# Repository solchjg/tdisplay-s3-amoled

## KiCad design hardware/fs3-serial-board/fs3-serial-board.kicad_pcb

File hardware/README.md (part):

# Hardware: producing the FeatherS3D survey boards

This folder holds three boards for the FeatherS3D site survey and the §40 build,
plus the generator that makes them. This page lists the steps from the design files
to a working set of boards. The design itself, and the reasons behind it, are in
[fs3-survey-carrier.md](../docs/Method/project/fs3-survey-carrier.md). Wiring sheets
[17](../docs/Method/project/wiring/wiring-17-fs3-carrier.png),
[19](../docs/Method/project/wiring/wiring-19-fs3-analog.png) and
[20](../docs/Method/project/wiring/wiring-20-fs3-serial.png) (where each part sits on the
carrier, the analog board and the serial board) and
[18](../docs/Method/project/wiring/wiring-18-fs3-boards.png) (the leads between the boards)
show how the boards fit together.

| Folder | Board | Size | Plugs into |
|---|---|---|---|
| [`fs3-survey-carrier/`](fs3-survey-carrier/) | The carrier: FeatherS3D on sockets, Notecarrier-X on posts, every connector | 110 × 90 mm | — |
| [`fs3-analog-board/`](fs3-analog-board/) | Isolated 4-20 mA loop and 0 – 5 V probe input (24 V field supply, ADS1115) | 74 × 54 mm | Carrier J12 |
| [`fs3-serial-board/`](fs3-serial-board/) | Isolated logic-level serial port for the MB7569 ultrasonic sensor | 63 × 54 mm | Carrier J13 |
| [`pcbgen/`](pcbgen/) | The shared scripts that make all three from each board's `netlist.py` | — | — |

Each board's `fab/` folder holds what a board house and an assembler need:

| File | Use |
|---|---|
| `<board>-gerbers.zip` | Gerbers and drill files, for the board house |
| `bom.csv` | The parts list: quantity, value, designators, footprint, part number |
| `positions.csv` | Part placement for an assembly service (origin at the bottom-left corner) |
| `cpl-jlc.csv`, `bom-jlc.csv` | The surface-mount parts' placement (CPL) and parts list in JLCPCB's columns |
| `cpl-jlc-all.csv`, `bom-jlc-all.csv` | The same for every fitted part, through-hole connectors, sockets and the key included |
| `centroid-pcbway.csv`, `bom-pcbway.csv` | Every fitted part's placement (centroid) and parts list in PCBWay's columns, each line marked SMD or THT |
| `assembly.pdf` | The top side with each part's designator, for hand assembly and for the fit checks below |
| `schematic.pdf` | The schematic |
| `top.png`, `bottom.png` | Pictures of the finished board |

## 1. Close the open checks

None of the boards has been built yet. Settle these before ordering. Each one is
explained in "Before ordering" in
[fs3-survey-carrier.md](../docs/Method/project/fs3-survey-carrier.md#before-ordering).

- [ ] **Notecarrier-X holes.** Check that a Notecarrier-X v1.3 has the v1.2 drawing's
      holes (58.49 × 30.48 mm) and that M2.5 posts fit them.
- [ ] **Feather footprint.** Print the carrier's `assembly.pdf` at 100 % and lay the
      FeatherS3D on it. RST (long header pin 1) must sit at the USB-C end, and BAT must be
      level with the long header's fifth pin.
- [ ] **Display cables.** Use a same-direction 8-way PH 2.0 lead for the e-paper (pin 1 to
      pin 1) and a standard straight 16-way IDC ribbon for the 3.12" OLED. Check that the OLED
      module's pin 3 is unconnected.
- [ ] **Qwiic pinout.** Pin 1 is GND and pin 4 is SCL.
- [ ] **Isolated DC-DCs.** Check the test duration of XP Power's IH "-H" 3 kVDC rating
      against C-40.6's 1 minute, and the IH0512S-H's pins against XP's drawing.
- [ ] **FSD §40.2.** It still names the Pololu #2808 as the display supply. The carrier
      uses an on-board TPS22917 instead. If you adopt the carrier, change that row in the FSD.

## 2. Order the boards

Upload each `fab/<board>-gerbers.zip` to a board house (JLCPCB, PCBWay, OSH Park and
similar). The settings are the same for all three:

- 2 layers, 1.6 mm FR-4, 1 oz copper
- HASL (lead-free) or ENIG finish, any solder mask colour
- Default rules: 0.2 mm (8 mil) track and space, 0.3 mm smallest drill
- No impedance control, no castellations, no V-scoring

The minimum order (usually 5) of each board is enough for spares.

To have the board house fit the surface-mount parts too, upload the BOM and placement
files with the Gerbers and fit the through-hole parts yourself afterwards:

- **JLCPCB:** `bom-jlc.csv` and `cpl-jlc.csv` hold only the surface-mount parts;
  `bom-jlc-all.csv` and `cpl-jlc-all.csv` add the through-hole parts, for JLCPCB to fit
  those too (at extra cost; check that each through-hole part is one it stocks).
  The `LCSC Part #` column is empty: fill it in, or pick each part in JLCPCB's matcher,
  checking it against the part number in the `Comment` column. In the placement
  preview, check each part's rotation and pin 1, above all the SOT-23, SOIC and TSSOP
  parts, the diodes and the Qwiic and microSD sockets. JLCPCB's library draws some
  footprints turned from KiCad's, and the preview lets you rotate a part to fix it.
- **PCBWay:** `bom-pcbway.csv` and `centroid-pcbway.csv`. They list every fitted part;
  the `Type` column says which are SMD and which THT, so you can delete the THT lines or
  note "do not place" against them to fit those parts yourself. Check rotations in the
  engineering query PCBWay sends before assembly, as for JLCPCB.
- **Other assemblers:** `bom.csv` and `positions.csv` (KiCad's format, all parts).

## 3. Order the parts

Each board's `bom.csv` lists its parts with a part number, or a generic description
for passives. The parts that need care when buying:

| Part | Board | Note |
|---|---|---|
| TPS22917DBVR | Carrier | Display supply switch; no substitute with the same pins |
| Molex 104031-0811 | Carrier | The microSD socket; its footprint is specific to it |
| Littelfuse 0466003.NR | Carrier | F1, the shared battery's 3 A fuse (1206) |
| XP Power IH0512S-H, IH0505S-H | Analog, serial | The isolated DC-DCs; the "-H" suffix is the 3 kVDC version |
| TI ISO1642DWR | Analog, serial | I2C isolator, wide SOIC-16 |
| TI ADS1115IDGSR | Analog | MSOP-10 with 0.5 mm pitch |
| Microchip DN2540N3-G | Analog | Current limiters, TO-92 |
| Vishay TNPW1206100RBEEA | Analog | R2, the 100 Ω 0.1 % loop shunt |
| 15 kΩ and 10 kΩ, 0.1 % | Analog | R14 and R15, the probe divider |
| Bourns 3296W-1-201LF | Analog | RV1 and RV2, 200 Ω trimmers |
| Phoenix MKDS 1,5 (5.08 mm) | Analog, serial | Field terminals: 2-way and 3-way (analog), 4-way (serial) |

Besides the boards' own parts, the build needs:

- **Feather sockets:** a 1 × 16 and a 1 × 12 2.54 mm female socket strip (in the BOM as
  J1 and J2).
- **Posts:** four M2.5 standoffs, at least 10 mm, for the Notecarrier-X; four M3 standoffs
  for the carrier's corners; four M3 standoffs for each add-on board.
- **Leads**, all straight (pin 1 to pin 1):
  - JST XH 6-way (carrier J12 to the analog board) and XH 4-way (J13 to the serial board)
  - JST XH 3-way for the key (J3)
  - JST PH 2-way leads from J23 to the Feather's battery socket and from J25 to the
    Notecarrier's, or one XH 2-way lead from J27 to the Notecarrier header for the
    shared battery (at most 150 mm, 22 AWG or heavier)
  - JST PH 2.0 8-way for the e-paper, or a 16-way IDC ribbon for the 3.12" OLED
  - Qwiic (JST SH 4-way) leads for the Feather's I2C2 socket, the RTC, the Notecarrier,
    the BME280 and the 1.3" OLED
- **Jumpers:** two 2.54 mm jumpers for J26, or a panel DPST switch and its lead.
- **Enclosure side:** a waterproof panel-mount USB-C socket; surge protectors and an earth
  rod for each field cable (C-40.7), which stay at the enclosure wall, not on the boards;
  cable glands.

## 4. Assemble

- **Carrier.** Solder the surface-mount parts first, then the through-hole connectors
  and the Feather socket strips. Leave JP1 open, so the Notecarrier's 3.3 V stays
  unconnected. Do not fit a cell to J24 or the Notecarrier's own socket if you will use
  the shared battery on J27.
- **Analog and serial boards.** Solder the surface-mount parts first. The ADS1115 has
  0.5 mm pitch and needs flux and a fine tip, or a hot-air station. Fit the DC-DC, the
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
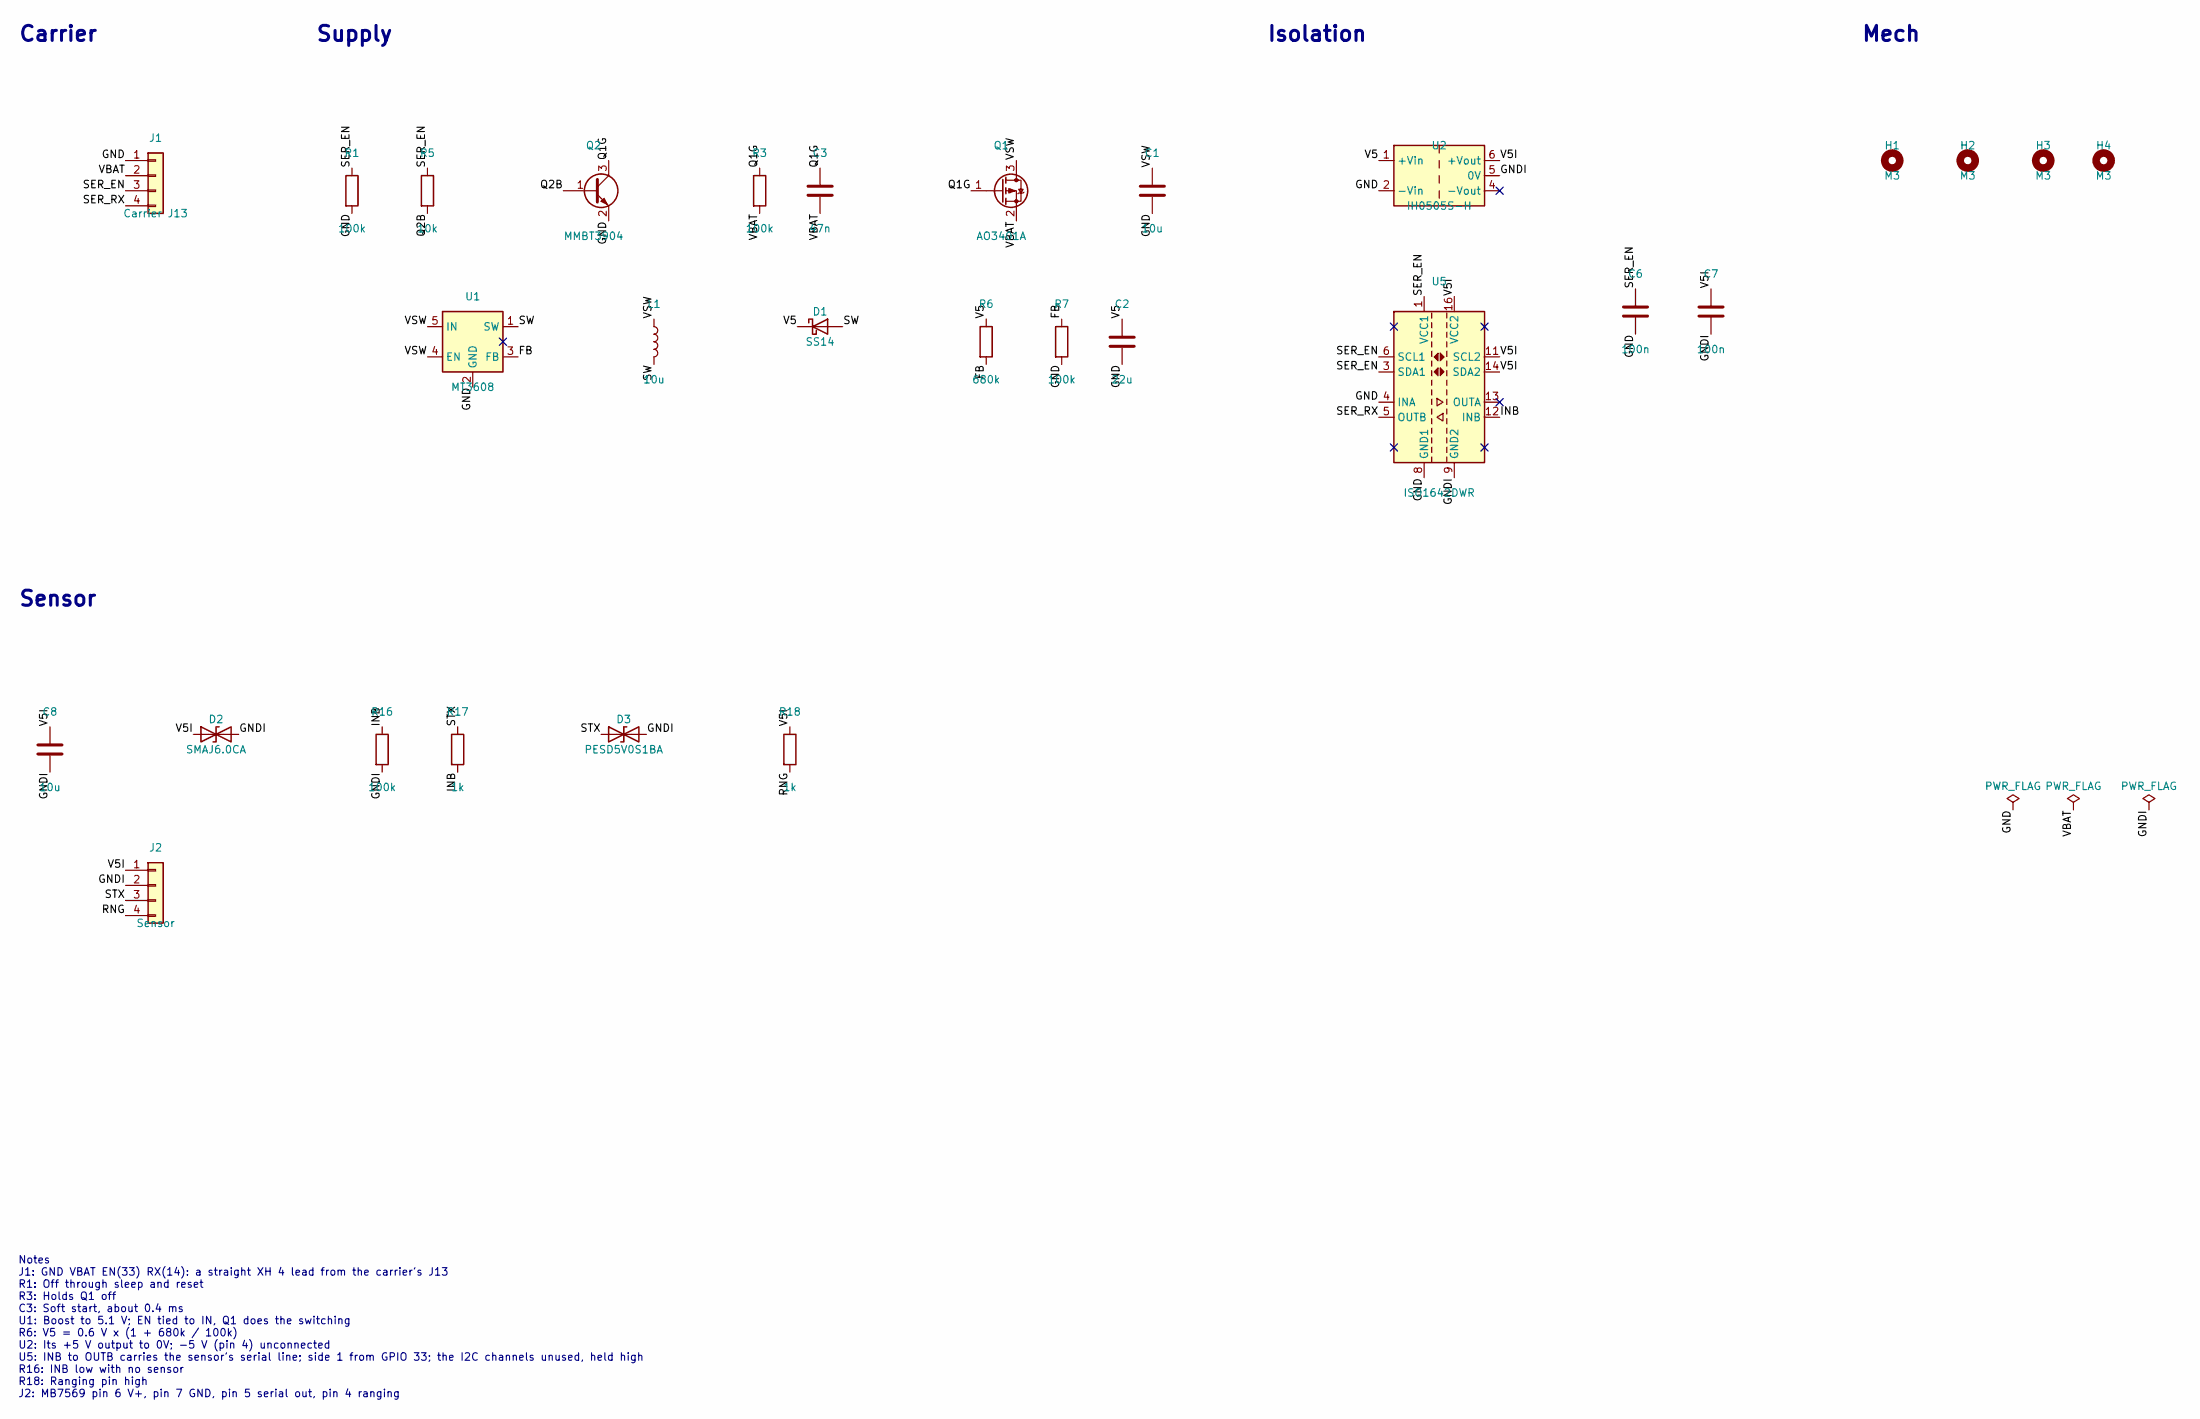
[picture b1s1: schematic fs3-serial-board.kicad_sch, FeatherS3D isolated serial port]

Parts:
C1, C8: 10u; C_0805_2012Metric
C2: 22u; C_1206_3216Metric; MPN 22 uF 1206 X5R 10 V
C3: 47n; C_0805_2012Metric
C6, C7: 100n; C_0805_2012Metric
D1: SS14; D_SMA; MPN SS14 (1 A, 40 V Schottky)
D2: SMAJ6.0CA; D_SMA; MPN SMAJ6.0CA
D3: PESD5V0S1BA; D_SOD-323; MPN Nexperia PESD5V0S1BA
H1, H2, H3, H4: M3; MountingHole_3.2mm_M3
J1: Carrier J13; JST_XH_B4B-XH-A_1x04_P2.50mm_Vertical; MPN JST B4B-XH-A
J2: Sensor; TerminalBlock_Phoenix_MKDS-1,5-4-5.08_1x04_P5.08mm_Horizont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; MPN Phoenix 1715747 (MKDS 1,5/4-5,08)
L1: 10u; L_Bourns_SRN6045TA; MPN Bourns SRN6045TA-100M (10 uH, 2.4 A)
Q1: AO3401A; SOT-23; MPN Alpha & Omega AO3401A (or DMG2305UX)
Q2: MMBT3904; SOT-23; MPN onsemi MMBT3904LT1G
R1, R3, R7, R16: 100k; R_0805_2012Metric
R5: 10k; R_0805_2012Metric
R6: 680k; R_0805_2012Metric
R17, R18: 1k; R_0805_2012Metric
U1: MT3608; SOT-23-6; MPN Aerosemi MT3608
U2: IH0505S-H; Converter_DCDC_XP_POWER-IHxxxxSH_THT; MPN XP Power IH0505S-H (2 W, 3 kVDC)
U5: ISO1642DWR; SOIC-16W_7.5x10.3mm_P1.27mm; MPN TI ISO1642DWR (5 kVrms)

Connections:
FB: R6.2, R7.1, U1.3 (FB)
GND: C1.2, C2.2, C6.2, J1.1, Q2.2 (E), R1.2, R7.2, U1.2 (GND), U2.2 (-Vin), U5.4 (INA), U5.8 (GND1)
GNDI: C7.2, C8.2, D2.2 (A2), D3.2 (A2), J2.2, R16.2, U2.5 (0V), U5.9 (GND2)
INB: R16.1, R17.2, U5.12 (INB)
Q1G: C3.1, Q1.1 (G), Q2.3 (C), R3.1
Q2B: Q2.1 (B), R5.2
RNG: J2.4, R18.2
SER_EN: C6.1, J1.3, R1.1, R5.1, U5.1 (VCC1), U5.3 (SDA1), U5.6 (SCL1)
SER_RX: J1.4, U5.5 (OUTB)
STX: D3.1 (A1), J2.3, R17.1
SW: D1.2 (A), L1.2, U1.1 (SW)
V5: C2.1, D1.1 (K), R6.1, U2.1 (+Vin)
V5I: C7.1, C8.1, D2.1 (A1), J2.1, R18.1, U2.6 (+Vout), U5.11 (SCL2), U5.14 (SDA2), U5.16 (VCC2)
VBAT: C3.2, J1.2, Q1.2 (S), R3.2
VSW: C1.1, L1.1, Q1.3 (D), U1.4 (EN), U1.5 (IN)

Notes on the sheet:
Notes J1: GND VBAT EN(33) RX(14): a straight XH 4 lead from the carrier's J13 R1: Off through sleep and reset R3: Holds Q1 off C3: Soft start, about 0.4 ms U1: Boost to 5.1 V; EN tied to IN, Q1 does the switching R6: V5 = 0.6 V x (1 + 680k / 100k) U2: Its +5 V output to 0V; -5 V (pin 4) unconnected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
Carrier
Supply
Isolation
Sensor
Mech

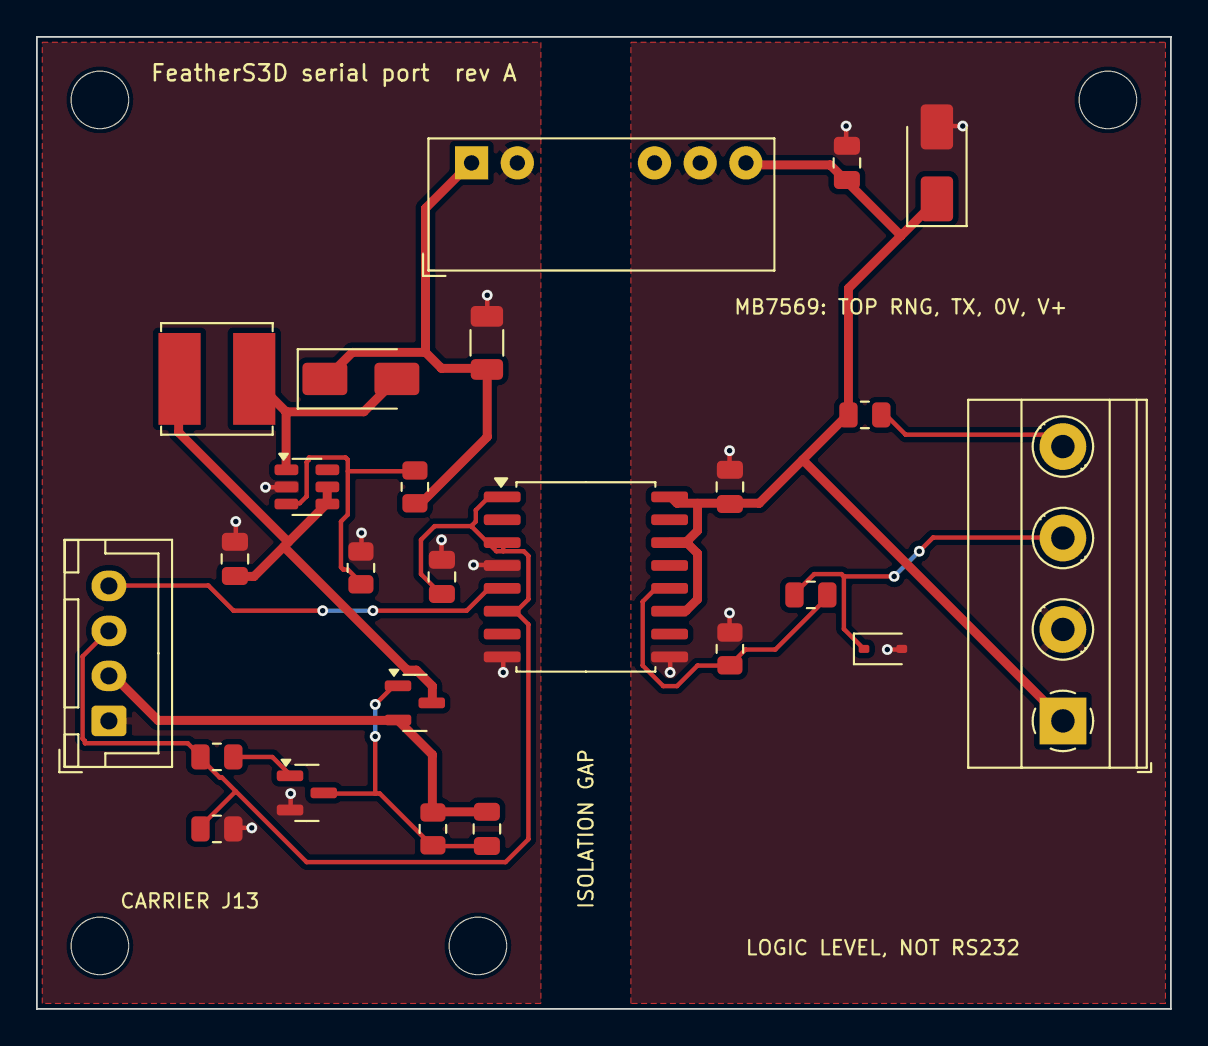
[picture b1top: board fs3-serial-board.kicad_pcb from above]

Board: 2 copper layers, 63.0 x 54.0 mm, 29 parts (0 on the bottom side), 15 nets.

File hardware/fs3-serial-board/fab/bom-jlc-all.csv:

Comment,Designator,Footprint,LCSC Part #
10u 0805 X5R 10 V,"C1,C8",C_0805_2012Metric,
22 uF 1206 X5R 10 V,C2,C_1206_3216Metric,
47n 0805 X7R 16 V,C3,C_0805_2012Metric,
100n 0805 X7R 50 V,"C6,C7",C_0805_2012Metric,
"SS14 (1 A, 40 V Schottky)",D1,D_SMA,
SMAJ6.0CA,D2,D_SMA,
Nexperia PESD5V0S1BA,D3,D_SOD-323,
JST B4B-XH-A,J1,JST_XH_B4B-XH-A_1x04_P2.50mm_Vertical,
"Phoenix 1715747 (MKDS 1,5/4-5,08)",J2,"TerminalBlock_Phoenix_MKDS-1,5-4-5.08_1x04_P5.08mm_Horizontal",
"Bourns SRN6045TA-100M (10 uH, 2.4 A)",L1,L_Bourns_SRN6045TA,
Alpha & Omega AO3401A (or DMG2305UX),Q1,SOT-23,
onsemi MMBT3904LT1G,Q2,SOT-23,
100k 0805 1 %,"R1,R3,R7,R16",R_0805_2012Metric,
10k 0805 1 %,R5,R_0805_2012Metric,
680k 0805 1 %,R6,R_0805_2012Metric,
1k 0805 1 %,"R17,R18",R_0805_2012Metric,
Aerosemi MT3608,U1,SOT-23-6,
"XP Power IH0505S-H (2 W, 3 kVDC)",U2,Converter_DCDC_XP_POWER-IHxxxxSH_THT,
TI ISO1642DWR (5 kVrms),U5,SOIC-16W_7.5x10.3mm_P1.27mm,

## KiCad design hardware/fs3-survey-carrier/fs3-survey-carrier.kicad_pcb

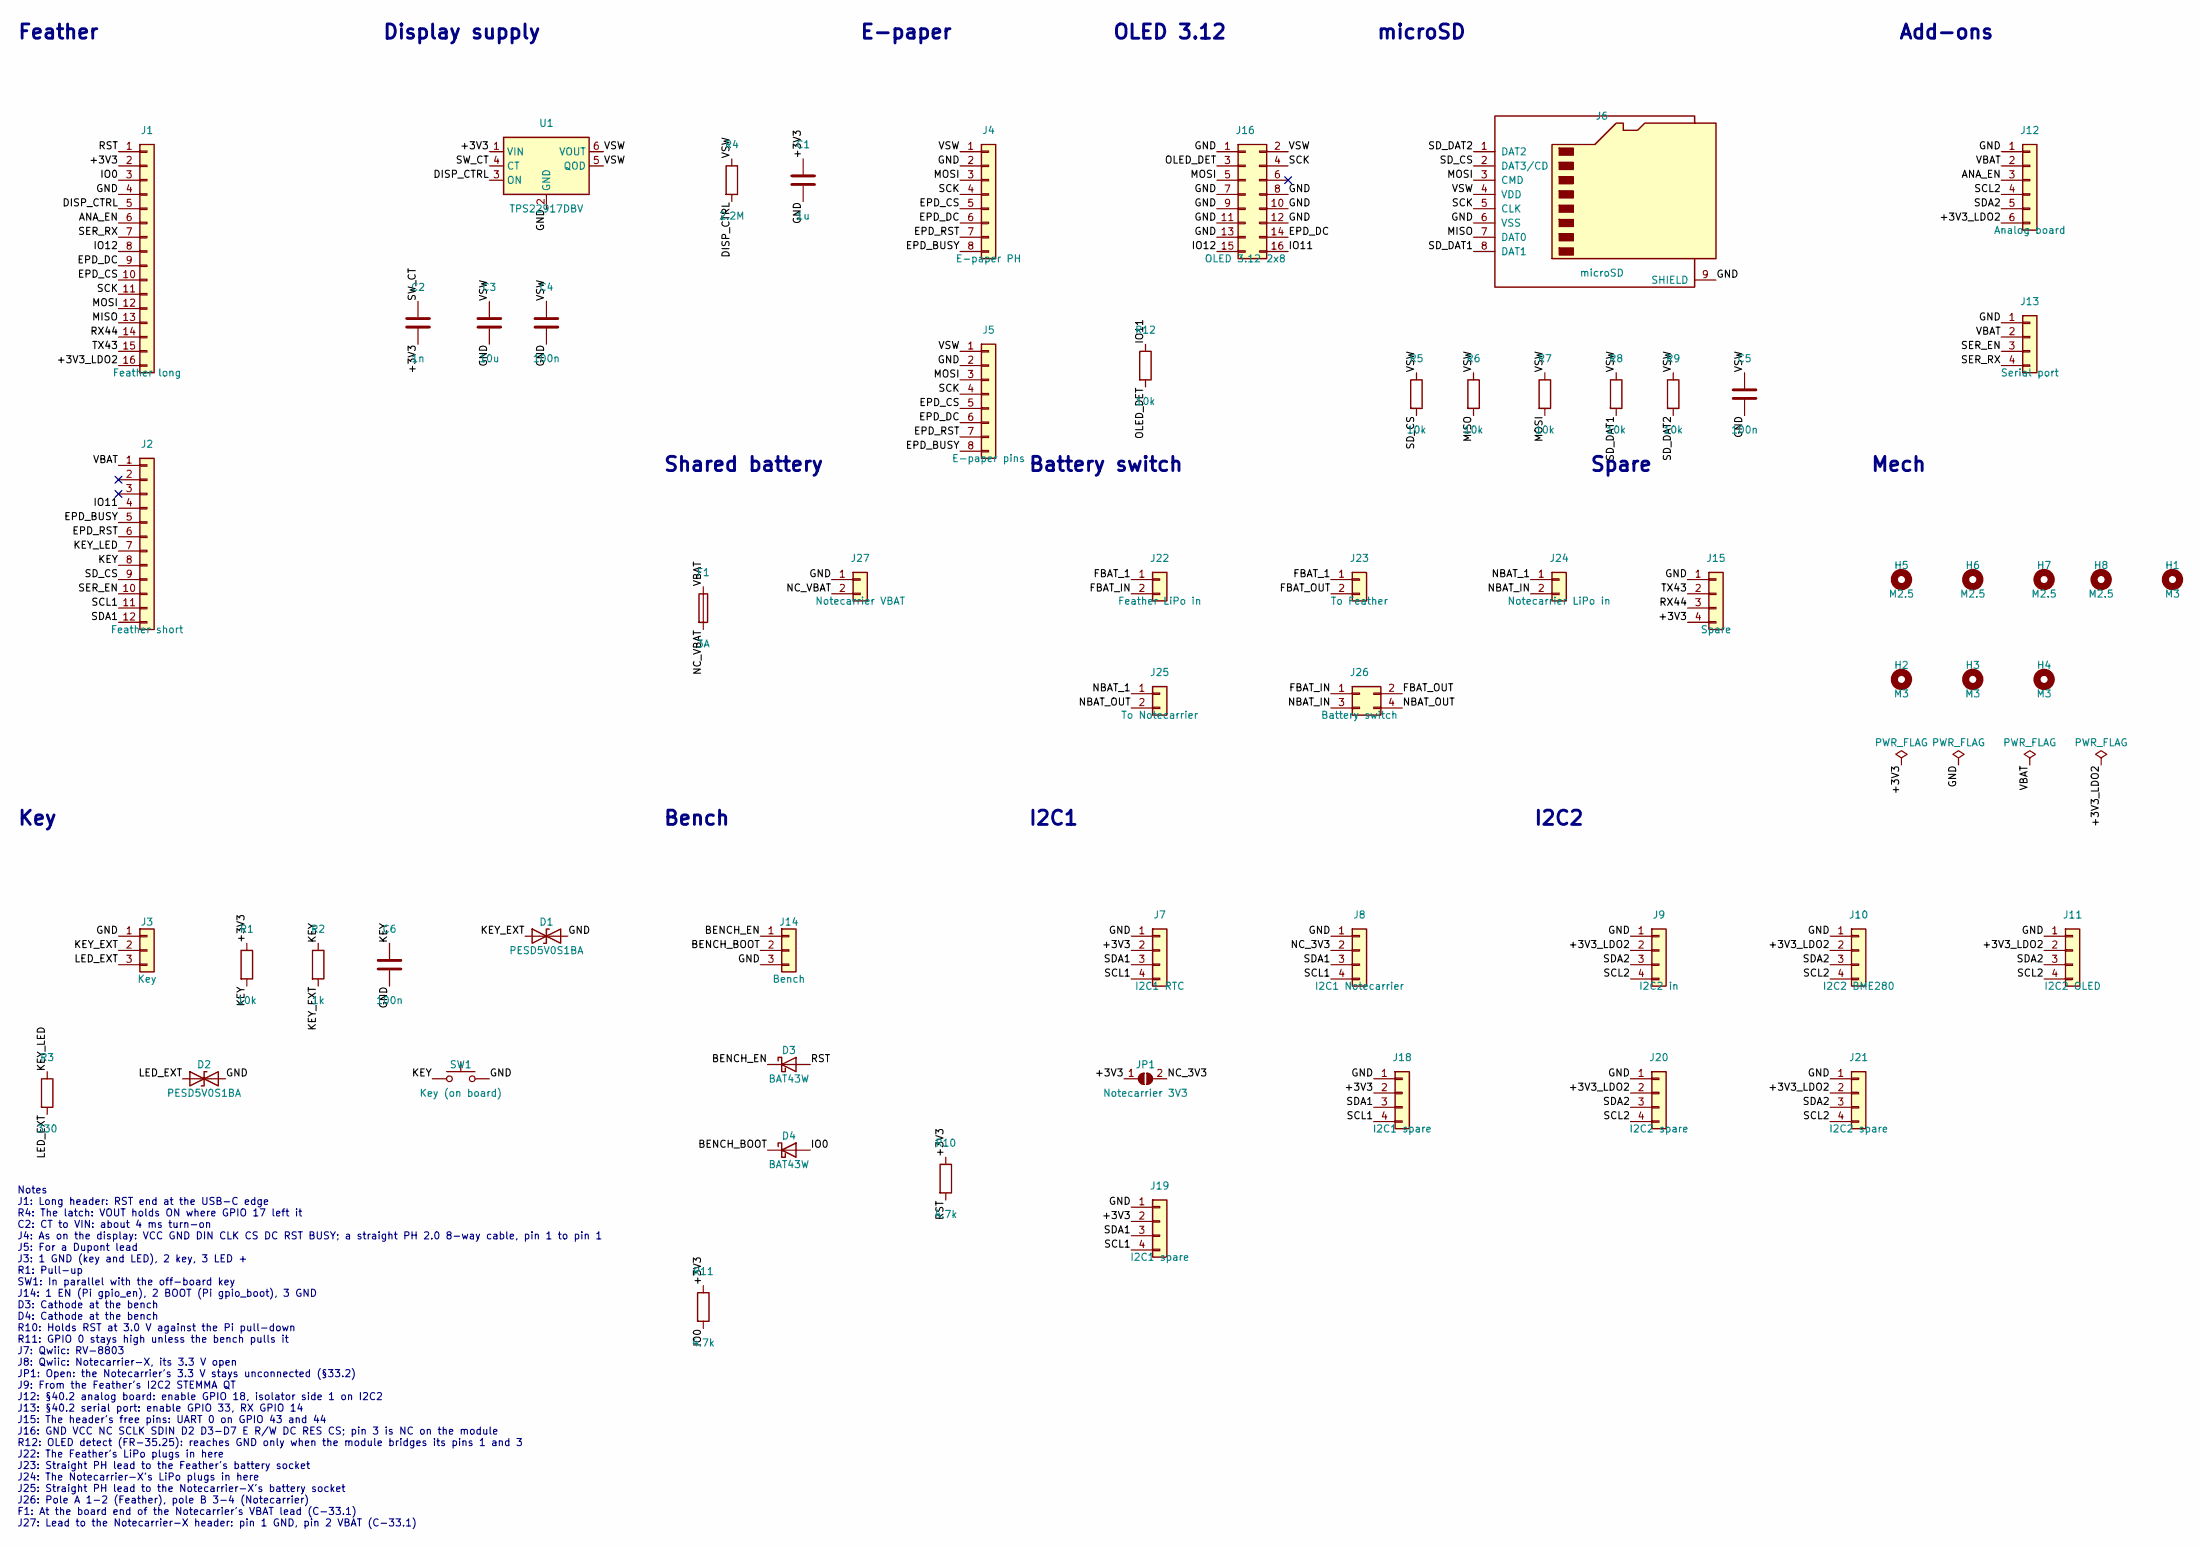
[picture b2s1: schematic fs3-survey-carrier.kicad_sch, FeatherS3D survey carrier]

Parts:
C1: 1u; C_0805_2012Metric
C2: 1n; C_0805_2012Metric
C3: 10u; C_0805_2012Metric
C4, C5, C6: 100n; C_0805_2012Metric
D1, D2: PESD5V0S1BA; D_SOD-323; MPN Nexperia PESD5V0S1BA
D3, D4: BAT43W; D_SOD-123; MPN BAT43W
F1: 3A; Fuse_1206_3216Metric; MPN Littelfuse 0466003.NR (3 A fast, 1206)
H1, H2, H3, H4: M3; MountingHole_3.2mm_M3
H5, H6, H7, H8: M2.5; MountingHole_2.7mm_M2.5
J1: Feather long; PinSocket_1x16_P2.54mm_Vertical; MPN Samtec SSW-116-01-T-S or any 1x16 2.54 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
J2: Feather short; PinSocket_1x12_P2.54mm_Vertical; MPN 1x12 2.54 mm socket
J3: Key; JST_XH_B3B-XH-A_1x03_P2.50mm_Vertical; MPN JST B3B-XH-A
J4: E-paper PH; JST_PH_B8B-PH-K_1x08_P2.00mm_Vertical; MPN JST B8B-PH-K-S
J5: E-paper pins; PinHeader_1x08_P2.54mm_Vertical; MPN 1x8 2.54 mm header
J6: microSD; microSD_HC_Molex_104031-0811; MPN Molex 104031-0811
J7: I2C1 RTC; JST_SH_SM04B-SRSS-TB_1x04-1MP_P1.00mm_Horizontal; MPN JST SM04B-SRSS-TB
J8: I2C1 Notecarrier; JST_SH_SM04B-SRSS-TB_1x04-1MP_P1.00mm_Horizontal; MPN JST SM04B-SRSS-TB
J9: I2C2 in; JST_SH_SM04B-SRSS-TB_1x04-1MP_P1.00mm_Horizontal; MPN JST SM04B-SRSS-TB
J10: I2C2 BME280; JST_SH_SM04B-SRSS-TB_1x04-1MP_P1.00mm_Horizontal; MPN JST SM04B-SRSS-TB
J11: I2C2 OLED; JST_SH_SM04B-SRSS-TB_1x04-1MP_P1.00mm_Horizontal; MPN JST SM04B-SRSS-TB
J12: Analog board; JST_XH_B6B-XH-A_1x06_P2.50mm_Vertical; MPN JST B6B-XH-A
J13: Serial port; JST_XH_B4B-XH-A_1x04_P2.50mm_Vertical; MPN JST B4B-XH-A
J14: Bench; PinHeader_1x03_P2.54mm_Vertical; MPN 1x3 2.54 mm header
J15: Spare; PinHeader_1x04_P2.54mm_Vertical; MPN 1x4 2.54 mm header
J16: OLED 3.12 2x8; IDC-Header_2x08_P2.54mm_Vertical; MPN 2x8 2.54 mm shrouded box header (e.g. A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
J18, J19: I2C1 spare; JST_SH_SM04B-SRSS-TB_1x04-1MP_P1.00mm_Horizontal; MPN JST SM04B-SRSS-TB
J20, J21: I2C2 spare; JST_SH_SM04B-SRSS-TB_1x04-1MP_P1.00mm_Horizontal; MPN JST SM04B-SRSS-TB
J22: Feather LiPo in; JST_PH_B2B-PH-K_1x02_P2.00mm_Vertical; MPN JST B2B-PH-K-S
J23: To Feather; JST_PH_B2B-PH-K_1x02_P2.00mm_Vertical; MPN JST B2B-PH-K-S
J24: Notecarrier LiPo in; JST_PH_B2B-PH-K_1x02_P2.00mm_Vertical; MPN JST B2B-PH-K-S
J25: To Notecarrier; JST_PH_B2B-PH-K_1x02_P2.00mm_Vertical; MPN JST B2B-PH-K-S
J26: Battery switch; PinHeader_2x02_P2.54mm_Vertical; MPN 2x2 2.54 mm header + 2 jumpers
J27: Notecarrier VBAT; JST_XH_B2B-XH-A_1x02_P2.50mm_Vertical; MPN JST B2B-XH-A
JP1: Notecarrier 3V3; SolderJumper-2_P1.3mm_Open_RoundedPad1.0x1.5mm
R1, R5, R6, R7, R8, R9, R12: 10k; R_0805_2012Metric
R2: 1k; R_0805_2012Metric
R3: 330; R_0805_2012Metric
R4: 2.2M; R_0805_2012Metric
R10, R11: 4.7k; R_0805_2012Metric
SW1: Key (on board); SW_PUSH_6mm; MPN 6 mm tactile, 4.3 mm or taller
U1: TPS22917DBV; SOT-23-6; MPN TI TPS22917DBVR

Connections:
+3V3: C1.1, C2.2, J1.2, J7.2, J15.4, J18.2, J19.2, JP1.1 (A), R1.1, R10.1, R11.1, U1.1 (VIN)
+3V3_LDO2: J1.16, J9.2, J10.2, J11.2, J12.6, J20.2, J21.2
ANA_EN: J1.6, J12.3
BENCH_BOOT: D4.1 (K), J14.2
BENCH_EN: D3.1 (K), J14.1
DISP_CTRL: J1.5, R4.2, U1.3 (ON)
EPD_BUSY: J2.5, J4.8, J5.8
EPD_CS: J1.10, J4.5, J5.5
EPD_DC: J1.9, J4.6, J5.6, J16.14
EPD_RST: J2.6, J4.7, J5.7
FBAT_1: J22.1, J23.1
FBAT_IN: J22.2, J26.1
FBAT_OUT: J23.2, J26.2
GND: C1.2, C3.2, C4.2, C5.2, C6.2, D1.2 (A2), D2.2 (A2), J1.4, J3.1, J4.2, J5.2, J6.6 (VSS), J6.9 (SHIELD), J6.11, J7.1, J7.MP, J8.1, J8.MP, J9.1, J9.MP, J10.1, J10.MP, J11.1, J11.MP, J12.1, J13.1, J14.3, J15.1, J16.1, J16.7, J16.8, J16.9, J16.10, J16.11, J16.12, J16.13, J18.1, J18.MP, J19.1, J19.MP, J20.1, J20.MP, J21.1, J21.MP, J27.1, SW1.2, U1.2 (GND)
IO0: D4.2 (A), J1.3, R11.2
IO11: J2.4, J16.16, R12.1
IO12: J1.8, J16.15
KEY: C6.1, J2.8, R1.2, R2.1, SW1.1
KEY_EXT: D1.1 (A1), J3.2, R2.2
KEY_LED: J2.7, R3.1
LED_EXT: D2.1 (A1), J3.3, R3.2
MISO: J1.13, J6.7 (DAT0), R6.2
MOSI: J1.12, J4.3, J5.3, J6.3 (CMD), J16.5, R7.2
NBAT_1: J24.1, J25.1
NBAT_IN: J24.2, J26.3
NBAT_OUT: J25.2, J26.4
NC_3V3: J8.2, JP1.2 (B)
NC_VBAT: F1.2, J27.2
OLED_DET: J16.3, R12.2
RST: D3.2 (A), J1.1, R10.2
RX44: J1.14, J15.3
SCK: J1.11, J4.4, J5.4, J6.5 (CLK), J16.4
SCL1: J2.11, J7.4, J8.4, J18.4, J19.4
SCL2: J9.4, J10.4, J11.4, J12.4, J20.4, J21.4
SDA1: J2.12, J7.3, J8.3, J18.3, J19.3
SDA2: J9.3, J10.3, J11.3, J12.5, J20.3, J21.3
SD_CS: J2.9, J6.2 (DAT3/CD), R5.2
SD_DAT1: J6.8 (DAT1), R8.2
SD_DAT2: J6.1 (DAT2), R9.2
SER_EN: J2.10, J13.3
SER_RX: J1.7, J13.4
SW_CT: C2.1, U1.4 (CT)
TX43: J1.15, J15.2
VBAT: F1.1, J2.1, J12.2, J13.2
VSW: C3.1, C4.1, C5.1, J4.1, J5.1, J6.4 (VDD), J16.2, R4.1, R5.1, R6.1, R7.1, R8.1, R9.1, U1.5 (QOD), U1.6 (VOUT)

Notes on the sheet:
Notes J1: Long header: RST end at the USB-C edge R4: The latch: VOUT holds ON where GPIO 17 left it C2: CT to VIN: about 4 ms turn-on J4: As on the display: VCC GND DIN CLK CS DC RST BUSY; a straight PH 2.0 8-way cable, pin 1 to pin 1 J5: For a Dupont lead J3: 1 GND (key and LED), 2 key, 3 LED + R1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
Feather
Display supply
E-paper
OLED 3.12
microSD
Add-ons
Mech
Battery switch
Spare
Shared battery
Key
Bench
I2C1
I2C2

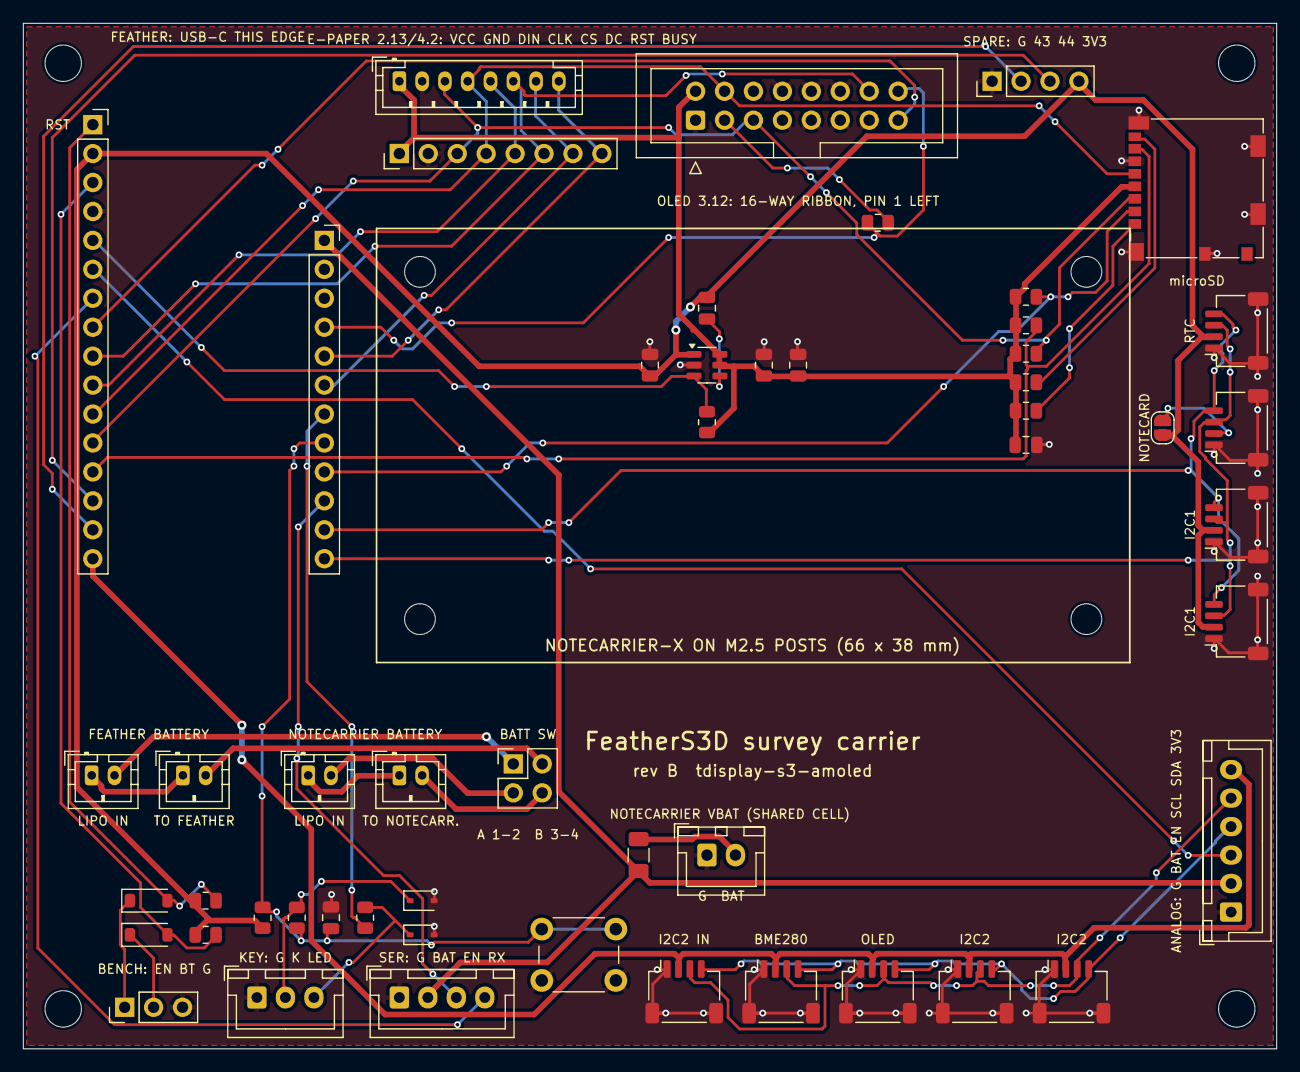
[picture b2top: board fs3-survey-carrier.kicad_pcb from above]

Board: 2 copper layers, 110.0 x 90.0 mm, 60 parts (0 on the bottom side), 45 nets.

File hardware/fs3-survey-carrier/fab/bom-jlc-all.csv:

Comment,Designator,Footprint,LCSC Part #
1u 0805 X7R 16 V,C1,C_0805_2012Metric,
1n 0805 C0G 50 V,C2,C_0805_2012Metric,
10u 0805 X5R 10 V,C3,C_0805_2012Metric,
100n 0805 X7R 16 V,"C4,C5,C6",C_0805_2012Metric,
Nexperia PESD5V0S1BA,"D1,D2",D_SOD-323,
BAT43W,"D3,D4",D_SOD-123,
"Littelfuse 0466003.NR (3 A fast, 1206)",F1,Fuse_1206_3216Metric,
Samtec SSW-116-01-T-S or any 1x16 2.54 mm socket,J1,PinSocket_1x16_P2.54mm_Vertical,
1x12 2.54 mm socket,J2,PinSocket_1x12_P2.54mm_Vertical,
JST B3B-XH-A,J3,JST_XH_B3B-XH-A_1x03_P2.50mm_Vertical,
JST B8B-PH-K-S,J4,JST_PH_B8B-PH-K_1x08_P2.00mm_Vertical,
1x8 2.54 mm header,J5,PinHeader_1x08_P2.54mm_Vertical,
Molex 104031-0811,J6,microSD_HC_Molex_104031-0811,
JST SM04B-SRSS-TB,"J7,J8,J9,J10,J11,J18,J19,J20,J21",JST_SH_SM04B-SRSS-TB_1x04-1MP_P1.00mm_Horizontal,
JST B6B-XH-A,J12,JST_XH_B6B-XH-A_1x06_P2.50mm_Vertical,
JST B4B-XH-A,J13,JST_XH_B4B-XH-A_1x04_P2.50mm_Vertical,
1x3 2.54 mm header,J14,PinHeader_1x03_P2.54mm_Vertical,
1x4 2.54 mm header,J15,PinHeader_1x04_P2.54mm_Vertical,
2x8 2.54 mm shrouded box header (e.g. Amphenol T821116A1S100CEU),J16,IDC-Header_2x08_P2.54mm_Vertical,
JST B2B-PH-K-S,"J22,J23,J24,J25",JST_PH_B2B-PH-K_1x02_P2.00mm_Vertical,
2x2 2.54 mm header + 2 jumpers,J26,PinHeader_2x02_P2.54mm_Vertical,
JST B2B-XH-A,J27,JST_XH_B2B-XH-A_1x02_P2.50mm_Vertical,
10k 0805 1 %,"R1,R5,R6,R7,R8,R9,R12",R_0805_2012Metric,
1k 0805 1 %,R2,R_0805_2012Metric,
330 0805 1 %,R3,R_0805_2012Metric,
2.2M 0805 1 %,R4,R_0805_2012Metric,
4.7k 0805 1 %,"R10,R11",R_0805_2012Metric,
"6 mm tactile, 4.3 mm or taller",SW1,SW_PUSH_6mm,
TI TPS22917DBVR,U1,SOT-23-6,

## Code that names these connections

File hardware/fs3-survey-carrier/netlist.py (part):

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    P("U1", ("Power_Management", "TPS22917DBV"), "TPS22917DBV", "Package_TO_SOT_SMD:SOT-23-6",
      {"1": V33, "2": GND, "3": "DISP_CTRL", "4": "SW_CT", "5": VSW, "6": VSW},
      "Display supply", (60.0, 30.0, 0), "TI TPS22917DBVR"),
    P("R4", R, "2.2M", FP["R"], pins(VSW, "DISP_CTRL"), "Display supply", (60.0, 35.0, 90),
      note="The latch: VOUT holds ON where GPIO 17 left it"),
    P("C1", C, "1u", FP["C"], pins(V33, GND), "Display supply", (55.0, 30.0, 90)),
    P("C2", C, "1n", FP["C"], pins("SW_CT", V33), "Display supply", (60.0, 25.0, 90),
      note="CT to VIN: about 4 ms turn-on"),
    P("C3", C, "10u", FP["C"], pins(VSW, GND), "Display supply", (65.0, 30.0, 90)),
    P("C4", C, "100n", FP["C"], pins(VSW, GND), "Display supply", (68.0, 30.0, 90)),
    # ---- e-paper: the Waveshare 8-way PH socket, the same on the 2.13" HAT and the 4.2" module
    P("J4", conn(8), "E-paper PH", "Connector_JST:JST_PH_B8B-PH-K_1x08_P2.00mm_Vertical",
      pins(VSW, GND, "MOSI", "SCK", "EPD_CS", "EPD_DC", "EPD_RST", "EPD_BUSY"),
      "E-paper", (33.0, 5.08, 0), "JST B8B-PH-K-S",
      "As on the display: VCC GND DIN CLK CS DC RST BUSY; a straight PH 2.0 8-way cable, pin 1 to pin 1"),
    P("J5", conn(8), "E-paper pins", "Connector_PinHeader_2.54mm:PinHeader_1x08_P2.54mm_Vertical",
      pins(VSW, GND, "MOSI", "SCK", "EPD_CS", "EPD_DC", "EPD_RST", "EPD_BUSY"),
      "E-paper", (33.0, 11.43, 90), "1x8 2.54 mm header", "For a Dupont lead"),
    # ---- microSD on the display supply, pull-ups as on Adafruit #4682
    P("J6", ("Connector", "Micro_SD_Card"), "microSD", "Connector_Card:microSD_HC_Molex_104031-0811",
      {"1": "SD_DAT2", "2": "SD_CS", "3": "MOSI", "4": VSW, "5": "SCK", "6": GND, "7": "MISO",
       "8": "SD_DAT1", "9": GND},
      "microSD", (103.0, 14.5, 90), "Molex 104031-0811"),
    P("R5", R, "10k", FP["R"], pins(VSW, "SD_CS"), "microSD", (88.0, 24.0, 0)),
    P("R6", R, "10k", FP["R"], pins(VSW, "MISO"), "microSD", (88.0, 26.5, 0)),
    P("R7", R, "10k", FP["R"], pins(VSW, "MOSI"), "microSD", (88.0, 29.0, 0)),
    P("R8", R, "10k", FP["R"], pins(VSW, "SD_DAT1"), "microSD", (88.0, 31.5, 0)),
    P("R9", R, "10k", FP["R"], pins(VSW, "SD_DAT2"), "microSD", (88.0, 34.0, 0)),
    P("C5", C, "100n", FP["C"], pins(VSW, GND), "microSD", (88.0, 37.0, 0)),
    # ---- the off-board illuminated key
    P("J3", conn(3), "Key", "Connector_JST:JST_XH_B3B-XH-A_1x03_P2.50mm_Vertical",
      pins(GND, "KEY_EXT", "LED_EXT"), "Key", (20.5, 85.5, 0), "JST B3B-XH-A",
      "1 GND (key and LED), 2 key, 3 LED +"),
    P("R1", R, "10k", FP["R"], pins(V33, "KEY"), "Key", (21.0, 78.5, 90), note="Pull-up"),
    P("R2", R, "1k", FP["R"], pins("KEY", "KEY_EXT"), "Key", (24.0, 78.5, 90)),
    P("C6", C, "100n", FP["C"], pins("KEY", GND), "Key", (27.0, 78.5, 90)),
    P("D1", ("Device", "D_TVS"), "PESD5V0S1BA", FP["TVS"], pins("KEY_EXT", GND), "Key",
      (35.0, 77.0, 0), "Nexperia PESD5V0S1BA"),
    P("R3", R, "330", FP["R"], pins("KEY_LED", "LED_EXT"), "Key", (30.0, 78.5, 90)),
    P("D2", ("Device", "D_TVS"), "PESD5V0S1BA", FP["TVS"], pins("LED_EXT", GND), "Key",
      (35.0, 80.0, 0), "Nexperia PESD5V0S1BA"),
    P("SW1", ("Switch", "SW_Push"), "Key (on board)", "Button_Switch_THT:SW_PUSH_6mm",
      pins("KEY", GND), "Key", (45.5, 79.5, 0), "6 mm tactile, 4.3 mm or taller",
      "In parallel with the off-board key"),
    # ---- the bench's EN and BOOT lines
    P("J14", conn(3), "Bench", "Connector_PinHeader_2.54mm:PinHeader_1x03_P2.54mm_Vertical",
      pins("BENCH_EN", "BENCH_BOOT", GND), "Bench", (8.89, 86.36, 90), "1x3 2.54 mm header",
      "1 EN (Pi gpio_en), 2 BOOT (Pi gpio_boot), 3 GND"),
    P("D3", ("Device", "D_Schottky"), "BAT43W", FP["SCH"], pins("BENCH_EN", "RST"), "Bench",
      (11.0, 77.0, 0), "BAT43W", "Cathode at the bench"),
    P("D4", ("Device", "D_Schottky"), "BAT43W", FP["SCH"], pins("BENCH_BOOT", "IO0"), "Bench",
      (11.0, 80.0, 0), "BAT43W", "Cathode at the bench"),
    P("R10", R, "4.7k", FP["R"], pins(V33, "RST"), "Bench", (16.0, 77.0, 0),
      note="Holds RST at 3.0 V against the Pi pull-down"),
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    # ---- the always-on bus I2C1 (no pull-ups here: the Feather's)
    P("J7", QW, "I2C1 RTC", FP["QWIIC"], pins(GND, V33, "SDA1", "SCL1"), "I2C1", (106.5, 27.0, 90),
      "JST SM04B-SRSS-TB", "Qwiic: RV-8803"),
    P("J8", QW, "I2C1 Notecarrier", FP["QWIIC"], pins(GND, "NC_3V3", "SDA1", "SCL1"), "I2C1",
      (106.5, 35.5, 90), "JST SM04B-SRSS-TB", "Qwiic: Notecarrier-X, its 3.3 V open"),
    P("JP1", ("Jumper", "SolderJumper_2_Open"), "Notecarrier 3V3",
      "Jumper:SolderJumper-2_P1.3mm_Open_RoundedPad1.0x1.5mm", pins(V33, "NC_3V3"), "I2C1",
      (100.0, 35.5, 90), note="Open: the Notecarrier's 3.3 V stays unconnected (§33.2)"),
    # ---- the switched bus I2C2: in from the Feather's I2C2 socket, out to the parts
    P("J9", QW, "I2C2 in", FP["QWIIC"], pins(GND, LDO2, "SDA2", "SCL2"), "I2C2", (58.0, 85.0, 0),
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      "JST SM04B-SRSS-TB"),
    # ---- add-on boards, keyed by pin count, pin 1 GND
    P("J12", conn(6), "Analog board", "Connector_JST:JST_XH_B6B-XH-A_1x06_P2.50mm_Vertical",
      pins(GND, VBAT, "ANA_EN", "SCL2", "SDA2", LDO2), "Add-ons", (106.0, 78.0, 90),
      "JST B6B-XH-A", "§40.2 analog board: enable GPIO 18, isolator side 1 on I2C2"),
    P("J13", conn(4), "Serial port", "Connector_JST:JST_XH_B4B-XH-A_1x04_P2.50mm_Vertical",
      pins(GND, VBAT, "SER_EN", "SER_RX"), "Add-ons", (33.0, 85.5, 0), "JST B4B-XH-A",
      "§40.2 serial port: enable GPIO 33, RX GPIO 14"),
    P("J15", conn(4), "Spare", "Connector_PinHeader_2.54mm:PinHeader_1x04_P2.54mm_Vertical",
      pins(GND, "TX43", "RX44", V33), "Spare", (85.026, 5.08, 90),
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       "14": "EPD_DC", "15": "IO12", "16": "IO11"},
      "OLED 3.12", (59.0, 8.5, 90), "2x8 2.54 mm shrouded box header (e.g. Amphenol T821116A1S100CEU)",
      "GND VCC NC SCLK SDIN D2 D3-D7 E R/W DC RES CS; pin 3 is NC on the module"),
    P("R12", R, "10k", FP["R"], pins("IO11", "OLED_DET"), "OLED 3.12", (75.0, 17.5, 0),
      note="OLED detect (FR-35.25): reaches GND only when the module bridges its pins 1 and 3"),
    # ---- spare Qwiic sockets, two on each bus
    P("J18", QW, "I2C1 spare", FP["QWIIC"], pins(GND, V33, "SDA1", "SCL1"), "I2C1", (106.5, 44.0, 90),
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    # Nothing here touches GND, so either battery polarity works. J26 takes two jumpers
    # (1-2 and 3-4) for no switch, or a lead to a panel DPST switch.
    P("J22", conn(2), "Feather LiPo in", "Connector_JST:JST_PH_B2B-PH-K_1x02_P2.00mm_Vertical",
      pins("FBAT_1", "FBAT_IN"), "Battery switch", (6.0, 66.0, 0), "JST B2B-PH-K-S",
      "The Feather's LiPo plugs in here"),
    P("J23", conn(2), "To Feather", "Connector_JST:JST_PH_B2B-PH-K_1x02_P2.00mm_Vertical",
      pins("FBAT_1", "FBAT_OUT"), "Battery switch", (14.0, 66.0, 0), "JST B2B-PH-K-S",
      "Straight PH lead to the Feather's battery socket"),
    P("J24", conn(2), "Notecarrier LiPo in", "Connector_JST:JST_PH_B2B-PH-K_1x02_P2.00mm_Vertical",
      pins("NBAT_1", "NBAT_IN"), "Battery switch", (25.0, 66.0, 0), "JST B2B-PH-K-S",
      "The Notecarrier-X's LiPo plugs in here"),
    P("J25", conn(2), "To Notecarrier", "Connector_JST:JST_PH_B2B-PH-K_1x02_P2.00mm_Vertical",
      pins("NBAT_1", "NBAT_OUT"), "Battery switch", (33.0, 66.0, 0), "JST B2B-PH-K-S",
      "Straight PH lead to the Notecarrier-X's battery socket"),
    P("J26", ("Connector_Generic", "Conn_02x02_Odd_Even"), "Battery switch",
      "Connector_PinHeader_2.54mm:PinHeader_2x02_P2.54mm_Vertical",
      pins("FBAT_IN", "FBAT_OUT", "NBAT_IN", "NBAT_OUT"), "Battery switch", (43.0, 65.0, 0),
      "2x2 2.54 mm header + 2 jumpers", "Pole A 1-2 (Feather), pole B 3-4 (Notecarrier)"),
    # ---- the shared cell (C-33.1): the Feather's VBAT through a 3 A fuse to a socket, and a
    # short lead (at most 150 mm, at least 22 AWG) from there to the Notecarrier-X header's
    # VBAT and GND. The Notecarrier's own LiPo socket (and so J24 / J25) and its USB-C then
    # carry nothing: two cells never join.
    P("F1", ("Device", "Fuse"), "3A", "Fuse:Fuse_1206_3216Metric", pins(VBAT, "NC_VBAT"),
      "Shared battery", (54.0, 73.0, 90), "Littelfuse 0466003.NR (3 A fast, 1206)",
      "At the board end of the Notecarrier's VBAT lead (C-33.1)"),
    P("J27", conn(2), "Notecarrier VBAT", "Connector_JST:JST_XH_B2B-XH-A_1x02_P2.50mm_Vertical",
      pins(GND, "NC_VBAT"), "Shared battery", (60.0, 73.0, 0), "JST B2B-XH-A",
      "Lead to the Notecarrier-X header: pin 1 GND, pin 2 VBAT (C-33.1)"),
    # ---- posts for the Notecarrier-X above the board (Blues 66.11 x 38.10 mm, holes 58.49 x 30.48 mm)
    P("H5", ("Mechanical", "MountingHole"), "M2.5", "MountingHole:MountingHole_2.7mm_M2.5", {}, "Mech",
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
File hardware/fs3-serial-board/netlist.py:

"""The FeatherS3D's isolated serial port (FSD §40.2, FR-40.12, C-40.4): the MaxBotix
MB7569-100's logic-level serial output (inverted, 9600 8N1) carried across an isolator to
UART 1 RX on GPIO 14, the sensor powered from an isolated DC-DC with its ranging pin (4) tied
high, so it ranges whenever powered. Logic levels only: a true RS232 instrument needs §30's
MAX3232 board.

It plugs into the carrier's J13 (XH 4: GND, VBAT, EN on GPIO 33, RX on GPIO 14). GPIO 33
switches the supply and powers the isolator's board side. Board side on the left, field side
on the right, a 5 mm copper-free gap between them. Run the ../pcbgen scripts from here.
"""
from parts import BOM_GENERIC as _BG, FP, GND, VBAT, C, P, R, conn, front_end, pins

GI, V5I = "GNDI", "V5I"
GAP = (28.0, 33.0)

PARTS = [
    P("J1", conn(4), "Carrier J13", "Connector_JST:JST_XH_B4B-XH-A_1x04_P2.50mm_Vertical",
      pins(GND, VBAT, "SER_EN", "SER_RX"), "Carrier", (4.0, 38.0, 90), "JST B4B-XH-A",
      "GND VBAT EN(33) RX(14): a straight XH 4 lead from the carrier's J13"),
] + front_end("SER_EN", {
    "R1": (10.0, 44.0, 0), "R5": (10.0, 40.0, 0), "Q2": (15.0, 42.0, 0), "R3": (22.0, 44.0, 90),
    "C3": (25.0, 44.0, 90), "Q1": (21.0, 37.0, 0), "C1": (11.0, 29.0, 90), "U1": (15.0, 25.0, 0),
    "L1": (10.0, 19.0, 0), "D1": (18.0, 19.0, 0), "R6": (21.0, 25.0, 90), "R7": (18.0, 29.5, 90),
    "C2": (25.0, 17.0, 90),
}, r6="680k") + [
    # ---- across the gap
    P("U2", ("Converter_DCDC", "IH0505SH"), "IH0505S-H", "Converter_DCDC:Converter_DCDC_XP_POWER-IHxxxxSH_THT",
      {"1": "V5", "2": GND, "4": None, "5": GI, "6": V5I}, "Isolation", (GAP[0] + 2.5 - 6.35, 7.0, 90),
      "XP Power IH0505S-H (2 W, 3 kVDC)", "Its +5 V output to 0V; -5 V (pin 4) unconnected"),
    P("U5", ("Isolator", "ISO1642DWR"), "ISO1642DWR", "Package_SO:SOIC-16W_7.5x10.3mm_P1.27mm",
      {"1": "SER_EN", "2": None, "3": "SER_EN", "4": GND, "5": "SER_RX", "6": "SER_EN", "7": None, "8": GND,
       "9": GI, "10": None, "11": V5I, "12": "INB", "13": None, "14": V5I, "15": None, "16": V5I},
      "Isolation", (sum(GAP) / 2, 30.0, 0), "TI ISO1642DWR (5 kVrms)",
      "INB to OUTB carries the sensor's serial line; side 1 from GPIO 33; the I2C channels unused, held high"),
    P("C6", C, "100n", FP["C"], pins("SER_EN", GND), "Isolation", (22.5, 30.0, 90)),
    P("C7", C, "100n", FP["C"], pins(V5I, GI), "Isolation", (38.5, 25.0, 90)),
    # ---- the sensor side
    P("C8", C, "10u", FP["C"], pins(V5I, GI), "Sensor", (45.0, 7.0, 90)),
    P("D2", ("Device", "D_TVS"), "SMAJ6.0CA", FP["SMA"], pins(V5I, GI), "Sensor", (50.0, 7.0, 90), "SMAJ6.0CA"),
    P("R16", R, "100k", FP["R"], pins("INB", GI), "Sensor", (38.5, 34.0, 90), note="INB low with no sensor"),
    P("R17", R, "1k", FP["R"], pins("STX", "INB"), "Sensor", (43.0, 31.0, 0)),
    P("D3", ("Device", "D_TVS"), "PESD5V0S1BA", FP["SOD323"], pins("STX", GI), "Sensor", (47.0, 34.0, 0),
      "Nexperia PESD5V0S1BA"),
    P("R18", R, "1k", FP["R"], pins(V5I, "RNG"), "Sensor", (46.0, 21.0, 0), note="Ranging pin high"),
    P("J2", conn(4), "Sensor", "TerminalBlock_Phoenix:TerminalBlock_Phoenix_MKDS-1,5-4-5.08_1x04_P5.08mm_Horizontal",
      pins(V5I, GI, "STX", "RNG"), "Sensor", (57.0, 38.0, 90), "Phoenix 1715747 (MKDS 1,5/4-5,08)",
      "MB7569 pin 6 V+, pin 7 GND, pin 5 serial out, pin 4 ranging"),
] + [
    P(f"H{k + 1}", ("Mechanical", "MountingHole"), "M3", FP["M3"], {}, "Mech", xy + (0,))
    for k, xy in enumerate([(3.5, 3.5), (3.5, 50.5), (24.5, 50.5), (59.5, 3.5)])
]

PAD_EXTRA = {}
POWER_NETS = {GND, VBAT, "VSW", "V5", "SW", GI, V5I}
BOARD_W, BOARD_H = 63.0, 54.0
GROUNDS = {GND: (0, 0, GAP[0], BOARD_H), GI: (GAP[1], 0, BOARD_W, BOARD_H)}
KEEPOUTS = [(GAP[0], 0, GAP[1], BOARD_H)]

NAME = "fs3-serial-board"
TITLE, DATE, REV = "FeatherS3D isolated serial port", "2026-11-20", "A"
SCH_NOTE = "FSD 40.2 serial port, FR-40.12, C-40.4; plugs into the carrier's J13"
SCH_LAYOUT = {"Carrier": (20, 35, 40), "Supply": (70, 35, 150), "Isolation": (230, 35, 90),
              "Sensor": (20, 130, 150), "Mech": (330, 35, 60)}
SCH_FLAGS = (GND, VBAT, GI)
SILK = [
    ("FeatherS3D serial port  rev A", 16.5, 2.0, 0.9, 0),
    ("CARRIER J13", 8.5, 48.0, 0.8, 0),
    ("ISOLATION GAP", sum(GAP) / 2, 44.0, 0.8, 90),
    ("MB7569: TOP RNG, TX, 0V, V+", 48.0, 15.0, 0.8, 0),
    ("LOGIC LEVEL, NOT RS232", 47.0, 50.6, 0.8, 0),
]
SILK_RECTS = []
ROUTE_FIRST = []
BOM_GENERIC = _BG

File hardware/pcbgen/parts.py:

"""Shared part helpers for the add-on boards' netlists, and their common front end:
a battery load switch on the enable line and a 5 V boost for the isolated DC-DC."""


def conn(n):
    return ("Connector_Generic", f"Conn_01x{n:02d}")


def pins(*nets):
    return {str(i + 1): n for i, n in enumerate(nets)}


def P(ref, sym, value, fp, nets, group, pcb, mpn="", note=""):
    return dict(ref=ref, lib=sym[0], sym=sym[1], value=value, fp=fp, pins=nets,
                group=group, pcb=pcb, mpn=mpn, note=note)


R = ("Device", "R")
C = ("Device", "C")
FP = {
    "R": "Resistor_SMD:R_0805_2012Metric",
    "R1206": "Resistor_SMD:R_1206_3216Metric",
    "C": "Capacitor_SMD:C_0805_2012Metric",
    "C1206": "Capacitor_SMD:C_1206_3216Metric",
    "SOT23": "Package_TO_SOT_SMD:SOT-23",
    "TO92": "Package_TO_SOT_THT:TO-92_Inline",
    "SMA": "Diode_SMD:D_SMA",
    "SMB": "Diode_SMD:D_SMB",
    "SOD323": "Diode_SMD:D_SOD-323",
    "TRIM": "Potentiometer_THT:Potentiometer_Bourns_3296W_Vertical",
    "M3": "MountingHole:MountingHole_3.2mm_M3",
}
GND, VBAT = "GND", "VBAT"


def front_end(en, at, r6="750k"):
    """The enable line's pull-down, the load switch (Q1, Q2) from VBAT and the MT3608 boost
    to 5.1 V (V5) for the isolated DC-DC. at: {ref: (x, y, rot)}; r6 sets the output:
    750k gives 5.1 V, 680k 4.7 V (0.6 V x (1 + R6 / 100k))."""
    g = "Supply"
    return [
        P("R1", R, "100k", FP["R"], pins(en, GND), g, at["R1"], note="Off through sleep and reset"),
        P("R5", R, "10k", FP["R"], pins(en, "Q2B"), g, at["R5"]),
        P("Q2", ("Transistor_BJT", "MMBT3904"), "MMBT3904", FP["SOT23"], {"1": "Q2B", "2": GND, "3": "Q1G"},
          g, at["Q2"], "onsemi MMBT3904LT1G"),
        P("R3", R, "100k", FP["R"], pins("Q1G", VBAT), g, at["R3"], note="Holds Q1 off"),
        P("C3", C, "47n", FP["C"], pins("Q1G", VBAT), g, at["C3"], note="Soft start, about 0.4 ms"),
        P("Q1", ("Transistor_FET", "AO3401A"), "AO3401A", FP["SOT23"], {"1": "Q1G", "2": VBAT, "3": "VSW"},
          g, at["Q1"], "Alpha & Omega AO3401A (or DMG2305UX)"),
        P("C1", C, "10u", FP["C"], pins("VSW", GND), g, at["C1"]),
        P("U1", ("Regulator_Switching", "MT3608"), "MT3608", "Package_TO_SOT_SMD:SOT-23-6",
          {"1": "SW", "2": GND, "3": "FB", "4": "VSW", "5": "VSW", "6": None}, g, at["U1"],
          "Aerosemi MT3608", "Boost to 5.1 V; EN tied to IN, Q1 does the switching"),
        P("L1", ("Device", "L"), "10u", "Inductor_SMD:L_Bourns_SRN6045TA", pins("VSW", "SW"), g, at["L1"],
          "Bourns SRN6045TA-100M (10 uH, 2.4 A)"),
        P("D1", ("Device", "D_Schottky"), "SS14", FP["SMA"], {"1": "V5", "2": "SW"}, g, at["D1"],
          "SS14 (1 A, 40 V Schottky)"),
        P("R6", R, r6, FP["R"], pins("V5", "FB"), g, at["R6"], note=f"V5 = 0.6 V x (1 + {r6} / 100k)"),
        P("R7", R, "100k", FP["R"], pins("FB", GND), g, at["R7"]),
        P("C2", C, "22u", FP["C1206"], pins("V5", GND), g, at["C2"], "22 uF 1206 X5R 10 V"),
    ]


BOM_GENERIC = {"100n": "0805 X7R 50 V", "10u": "0805 X5R 10 V", "47n": "0805 X7R 16 V",
               "1u": "1206 X7R 50 V"}
